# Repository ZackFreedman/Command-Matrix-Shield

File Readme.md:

The Command Matrix Shield is an expansion board for the ChipKit Uno32 that features an 8x8 LED matrix. The Command Matrix is bidirectional - you can display stuff on it, and sense light hitting it, simultaneously! It's the world's tiniest and most adorable touchscreen!

Important: This shield and the sketches are designed for ChipKIT, specifically the Uno32. THE CODE WILL NOT COMPILE UNDER ARDUINO - JUST MPIDE TARGETING THE UNO32. 

EAGLE files are stored in the folder "Command Matrix Shield PCB".

A straightforward debug program is in the folder "Command Matrix Shield Test". Expected behavior is to send coordinates over hardware serial at 9600 baud when a strong green or blue point light is shone at one of the pixels.

The software and hardware contain a large number of oversights, hacks, cut corners, and plain wrong decisions. Nevertheless, this is known working. Somehow.

Created by Zack Freedman of Voidstar Lab.
@ZackFreedman
yourstruly at zackfreedman com
zackfreedman.com
voidstarlab.com

For more information, visit http://zackfreedman.com/projects/command-matrix-shield/.

The Command Matrix Shield is open hardware licensed under Creative Commons Noncommercial Attribution. More permissive licenses are available on request.

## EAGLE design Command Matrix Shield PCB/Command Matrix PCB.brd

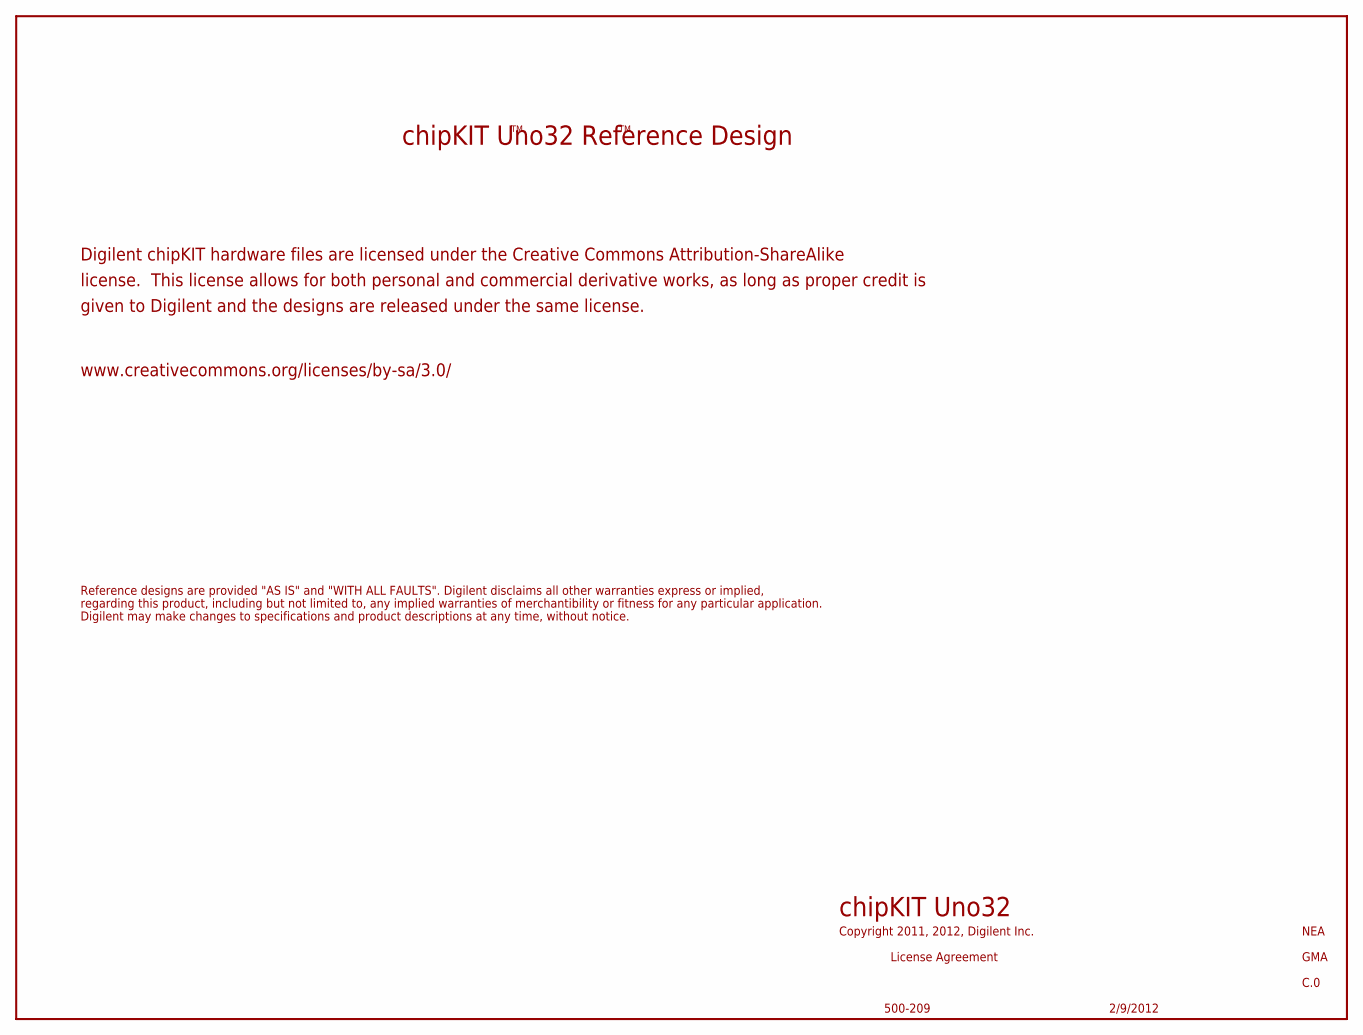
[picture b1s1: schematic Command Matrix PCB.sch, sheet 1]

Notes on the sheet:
Copyright 2011, 2012, Digilent Inc.
NEA
GMA
License Agreement
500-209
chipKIT Uno32
C.0
2/9/2012
Digilent chipKIT hardware files are licensed under the Creative Commons Attribution-ShareAlike
license. This license allows for both personal and commercial derivative works, as long as proper credit is
given to Digilent and the designs are released under the same license.
chipKIT Uno32 Reference Design
Reference designs are provided "AS IS" and "WITH ALL FAULTS". Digilent disclaims all other warranties express or implied,
regarding this product, including but not limited to, any implied warranties of merchantibility or fitness for any particular application.
Digilent may make changes to specifications and product descriptions at any time, without notice.
www.creativecommons.org/licenses/by-sa/3.0/

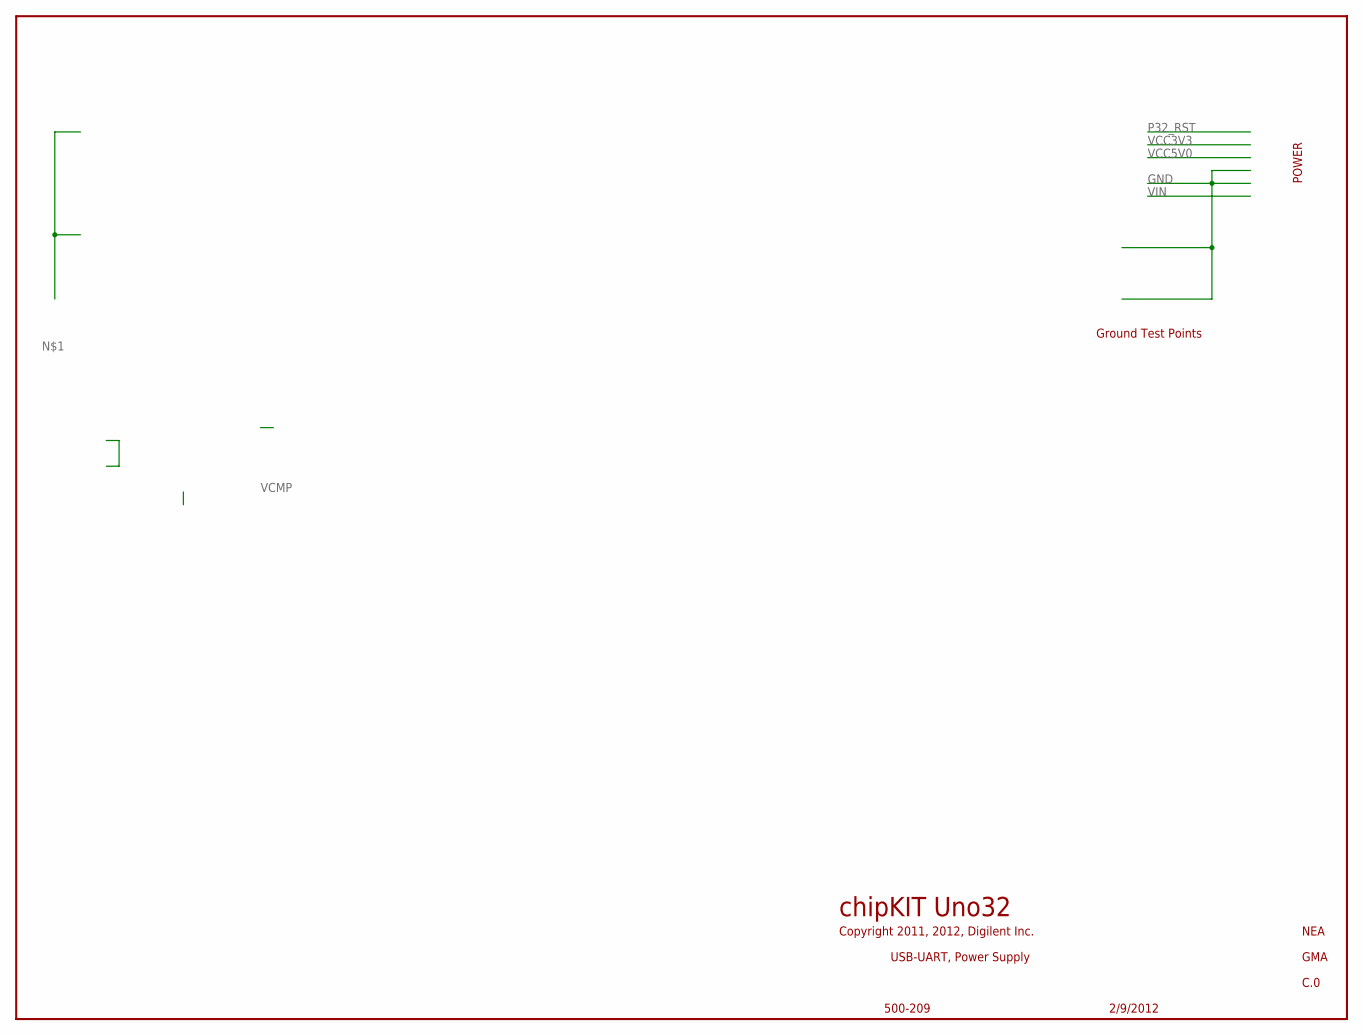
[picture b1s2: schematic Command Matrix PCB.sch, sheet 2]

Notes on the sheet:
POWER
Copyright 2011, 2012, Digilent Inc.
NEA
GMA
USB-UART, Power Supply
500-209
chipKIT Uno32
C.0
2/9/2012
Ground Test Points

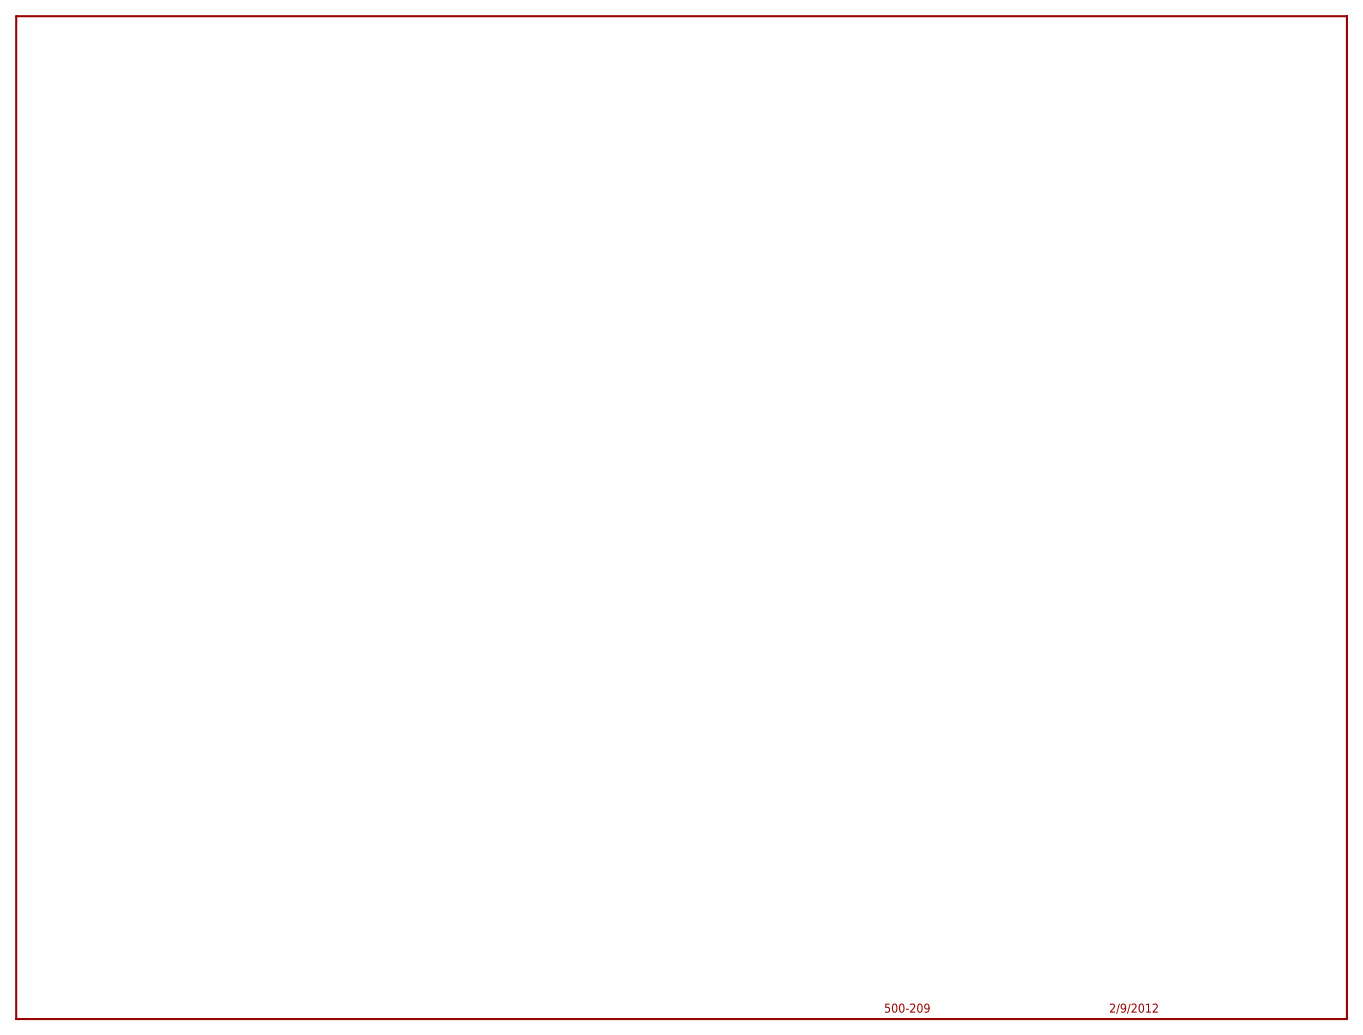
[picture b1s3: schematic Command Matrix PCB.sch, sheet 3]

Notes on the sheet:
500-209
2/9/2012

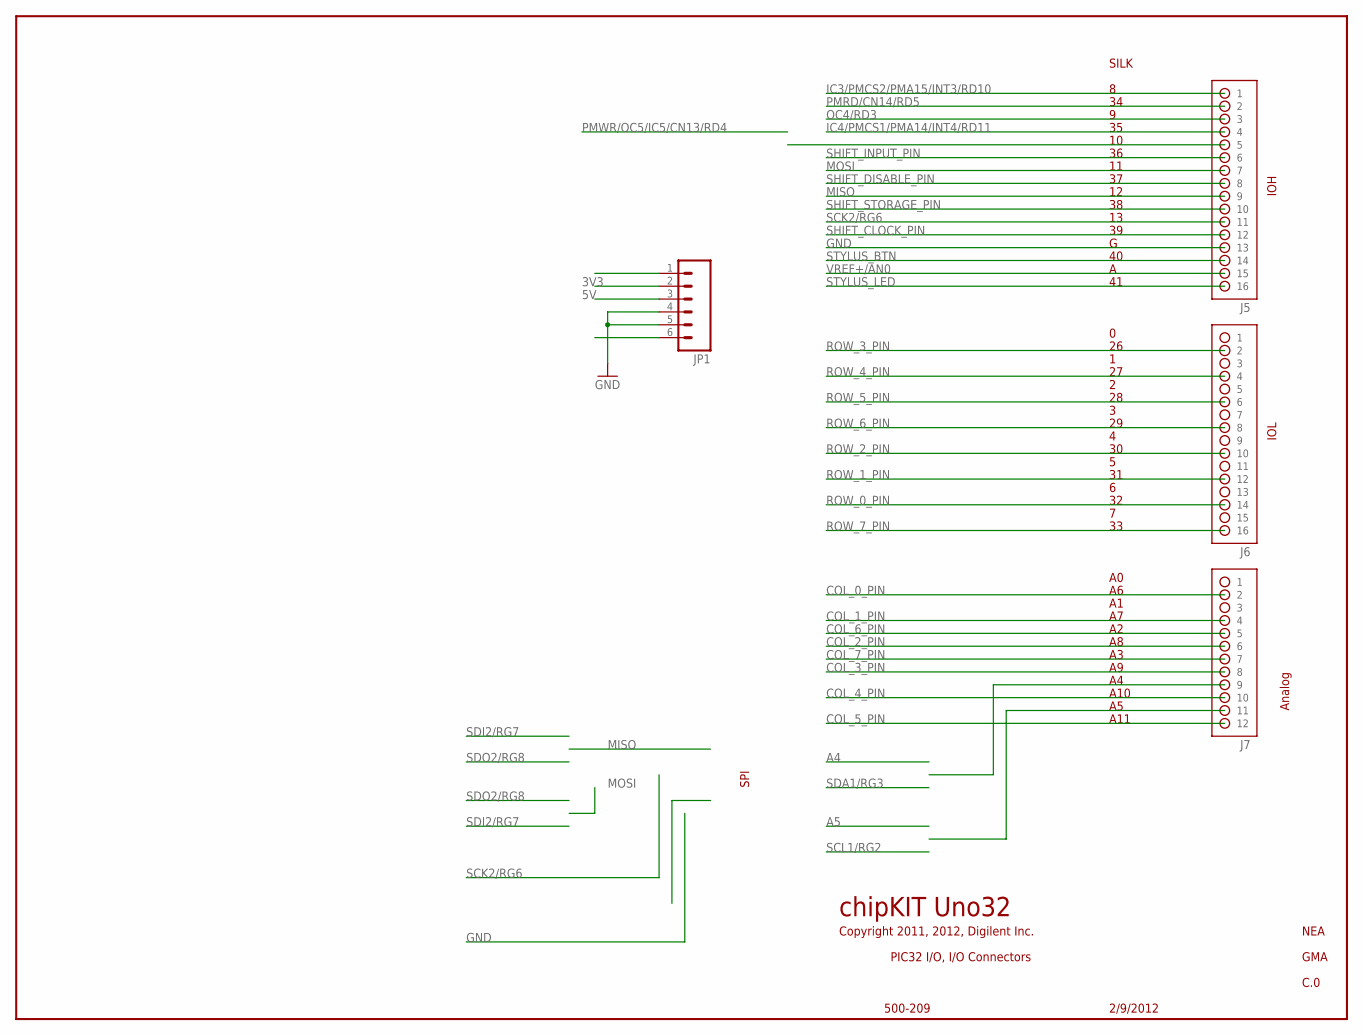
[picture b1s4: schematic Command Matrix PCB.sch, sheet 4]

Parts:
J5, J6: HDR-2X8
J7: HDR-2X6
JP1: M06SIP; 1X06

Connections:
3V3: JP1.2; also elsewhere on the board
5V: JP1.3; also elsewhere on the board
COL_0_PIN: J7.2; also elsewhere on the board
COL_1_PIN: J7.4; also elsewhere on the board
COL_2_PIN: J7.6; also elsewhere on the board
COL_3_PIN: J7.8; also elsewhere on the board
COL_4_PIN: J7.10; also elsewhere on the board
COL_5_PIN: J7.12; also elsewhere on the board
COL_6_PIN: J7.5; also elsewhere on the board
COL_7_PIN: J7.7; also elsewhere on the board
GND: J5.13, JP1.4, JP1.5; also elsewhere on the board
IC3/PMCS2/PMA15/INT3/RD10: J5.1
IC4/PMCS1/PMA14/INT4/RD11: J5.4
MISO: J5.9
MOSI: J5.7
OC4/RD3: J5.3
PMRD/CN14/RD5: J5.2
RESET: JP1.1
ROW_0_PIN: J6.14; also elsewhere on the board
ROW_1_PIN: J6.12; also elsewhere on the board
ROW_2_PIN: J6.10; also elsewhere on the board
ROW_3_PIN: J6.2; also elsewhere on the board
ROW_4_PIN: J6.4; also elsewhere on the board
ROW_5_PIN: J6.6; also elsewhere on the board
ROW_6_PIN: J6.8; also elsewhere on the board
ROW_7_PIN: J6.16; also elsewhere on the board
SCK2/RG6: J5.11
SHIFT_CLOCK_PIN: J5.12; also elsewhere on the board
SHIFT_DISABLE_PIN: J5.8; also elsewhere on the board
SHIFT_INPUT_PIN: J5.6; also elsewhere on the board
SHIFT_STORAGE_PIN: J5.10; also elsewhere on the board
STYLUS_BTN: J5.14; also elsewhere on the board
STYLUS_LED: J5.16; also elsewhere on the board
VREF+/AN0: J5.15

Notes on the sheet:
IOH
IOL
Analog
SPI
chipKIT Uno32
Copyright 2011, 2012, Digilent Inc.
NEA
PIC32 I/O, I/O Connectors
500-209
GMA
A10
A11
SILK
C.0
2/9/2012

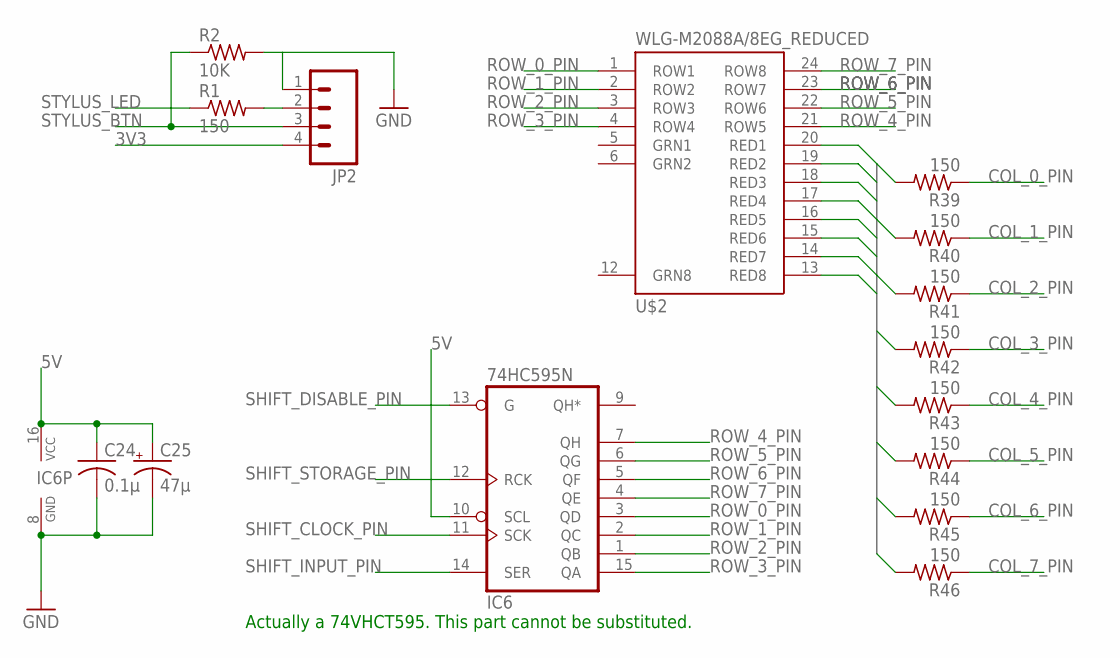
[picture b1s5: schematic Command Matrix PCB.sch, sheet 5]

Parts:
C24: 0.1µ; C025-025X050
C25: 47µ; E2,5-6E
IC6: 74HC595N; DIL16
JP2: M04PTH; 1X04
R1, R39, R40, R41, R42, R43, R44, R45, R46: 150; 0207/10
R2: 10K; 0207/10
U$2: WLG-M2088A/8EG_REDUCED

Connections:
3V3: JP2.4; also elsewhere on the board
5V: C24.1, C25.+, IC6.10 (SCL), IC6.16 (VCC); also elsewhere on the board
COLUMN_0: R39.2, U$2.20 (RED1)
COLUMN_1: R40.2, U$2.19 (RED2)
COLUMN_2: R41.2, U$2.18 (RED3)
COLUMN_3: R42.2, U$2.17 (RED4)
COLUMN_4: R43.2, U$2.16 (RED5)
COLUMN_5: R44.2, U$2.15 (RED6)
COLUMN_6: R45.2, U$2.14 (RED7)
COLUMN_7: R46.2, U$2.13 (RED8)
COL_0_PIN: R39.1; also elsewhere on the board
COL_1_PIN: R40.1; also elsewhere on the board
COL_2_PIN: R41.1; also elsewhere on the board
COL_3_PIN: R42.1; also elsewhere on the board
COL_4_PIN: R43.1; also elsewhere on the board
COL_5_PIN: R44.1; also elsewhere on the board
COL_6_PIN: R45.1; also elsewhere on the board
COL_7_PIN: R46.1; also elsewhere on the board
GND: C24.2, C25.-, IC6.8 (GND), JP2.1, R2.2; also elsewhere on the board
unnamed: JP2.2, R1.2
ROW_0_PIN: IC6.3 (QD), U$2.1 (ROW1); also elsewhere on the board
ROW_1_PIN: IC6.2 (QC), U$2.2 (ROW2); also elsewhere on the board
ROW_2_PIN: IC6.1 (QB), U$2.3 (ROW3); also elsewhere on the board
ROW_3_PIN: IC6.15 (QA), U$2.4 (ROW4); also elsewhere on the board
ROW_4_PIN: IC6.7 (QH), U$2.21 (ROW5); also elsewhere on the board
ROW_5_PIN: IC6.6 (QG), U$2.22 (ROW6); also elsewhere on the board
ROW_6_PIN: IC6.5 (QF), U$2.23 (ROW7); also elsewhere on the board
ROW_7_PIN: IC6.4 (QE), U$2.24 (ROW8); also elsewhere on the board
SHIFT_CLOCK_PIN: IC6.11 (SCK); also elsewhere on the board
SHIFT_DISABLE_PIN: IC6.13 (G); also elsewhere on the board
SHIFT_INPUT_PIN: IC6.14 (SER); also elsewhere on the board
SHIFT_STORAGE_PIN: IC6.12 (RCK); also elsewhere on the board
STYLUS_BTN: JP2.3, R2.1; also elsewhere on the board
STYLUS_LED: R1.1; also elsewhere on the board

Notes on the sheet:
Actually a 74VHCT595. This part cannot be substituted.

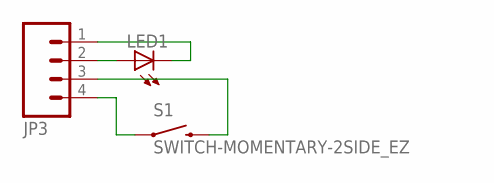
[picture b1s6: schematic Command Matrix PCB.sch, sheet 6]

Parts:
JP3: M04PTH; 1X04
LED1: LEDSIDEWAYS
S1: SWITCH-MOMENTARY-2SIDE_EZ; TACTILE-PTH-SIDEEZ

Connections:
unnamed: JP3.2, LED1.P$1 (A)
unnamed: JP3.1, LED1.P$2 (C)
unnamed: JP3.3, S1.2
unnamed: JP3.4, S1.1

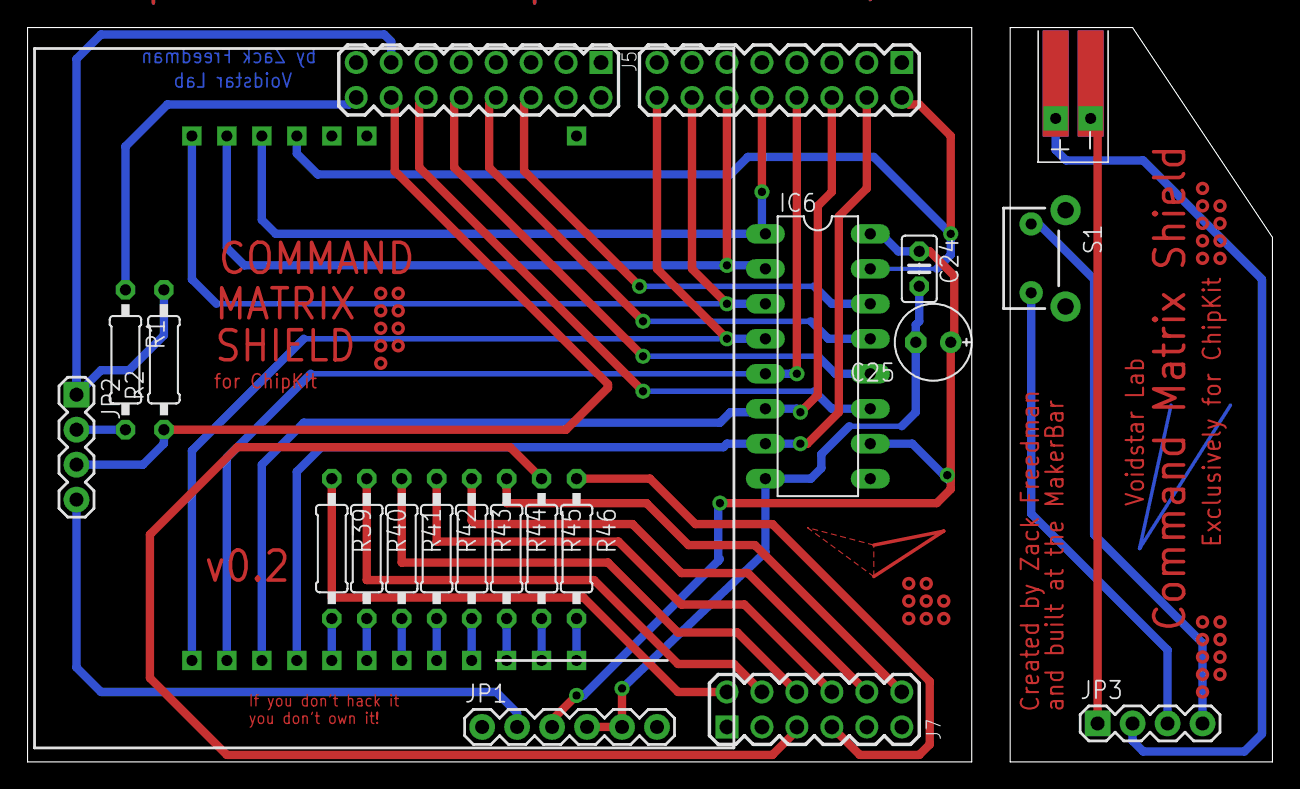
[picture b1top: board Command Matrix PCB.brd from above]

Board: 4 copper layers, 90.4 x 53.3 mm, 22 parts (0 on the bottom side), 38 nets.

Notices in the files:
parts and their libraries:
SparkFun-Connectors: Licensing: CC v3.0 Share-Alike You are welcome to use this library for commercial purposes.
